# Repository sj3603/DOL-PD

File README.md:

# DOL-PD
A repository for the DOL-PD project, implementing USB-C PD support for the Gamecube!
<!--- Once you have a logo for the project, put it here!  -->
<br>
<p align="justify">DOL-PD is a power switch board replacement for the Gamecube. Bulky Gamecube power brick taking up media center space? Need a less cluttered solution for your tournament setups? Or do you just not have access to an old Gamecube power brick anymore? Just swap out your power board with the DOL-PD and enjoy the convenience of running your Gamecube with USB-C off of a readily available USB-PD wall charger! The project is completely open source. Make it, sell it, improve it, whatever you can think of! Bringing your Gamecube into the modern age has never been easier with this board.</p>
<br>
<p align="justify"><em>Make sure to reference the license information at the bottom for more info</em></p>

## PARTS LIST
* [Parts List](https://docs.google.com/spreadsheets/d/1rPVbGJX8rQoN7rI187_ITezFnfsLrNyPKBN4Mu2_UrU/edit?usp=sharing)

*Be sure to use the list of parts under the V1 sheet! V2 is still in development and does not have finalized components*

*Note: V1 currently utilizes HDR's 3D printed enclosure for the USB-C port. This enclosure is free to use under the CC BY-NC-ND 4.0 License, and therefore is free to use and redistribute, however is NOT USABLE FOR SALE. If you plan to use the DOL-PD to produce your own boards for sale, you must create your own USB-C shroud. In the future, I may release a modified V1 board that uses an alternative USB-C port with a 3D printed enclosure of my own design that will be free use.*

## BOARD ASSEMBLY INSTRUCTIONS
* [V1 Assembly Instructions](https://docs.google.com/document/d/1EoNc1ywIzINfLsrusN0_Oh6O5GwIsG2bt14rkOoPlFw/edit?usp=sharing)

*An in depth board assembly instructional video is coming soon! In the meantime, a rudimentary google doc will be provided in its place.*

## SYSTEM INSTALL INSTRUCTIONS
* [Install Instructions](https://docs.google.com/document/d/1jQh1p8UBnYjq_hNC_C3m5ErBJNf1RWyx2jeYvmH2byE/edit?usp=sharing)

## THE FUTURE OF DOL-PD
As of 9/3/2023, DOL-PD V1 has been completed and released publicly. Going forward, there are 3 main goals for the DOL-PD project:
* Create DOL-PD V2, utilizing an integrated buck converter to allow the Gamecube to take in 15V and step down to 12V. This should greatly increase compatibility with USB-PD chargers. V2 is also planned to utilize a different USB-C port from V1 to allow for a complete no-cut solution. I may also re-release V1 with this alternate USB-C port.
* Create DOL-PD Rev-B, giving users the option to transfer their original Gamecube power button to maintain original power button feel and functionality.
* Create DOL-PD EXT, an external version of DOL-PD that will not require any internal modification of the Gamecube. This will however require custom sourced Gamecube Male power port molds.

## SPECIAL THANKS
This project couldn't have been possible without help from members of the Bitbuilt community, but I'd also like to give a special thanks to these modders, go check them out!
* [YveltalGriffin](https://github.com/mackieks) - For his amazing help troubleshooting and teaching me about pcb design and routing! 
* [Greg from Laser Bear Industries](https://twitter.com/collingall) - For his help researching parts and understanding power management! (Check out his shop for some other cool GameCube mods!)
* [HDR](https://ko-fi.com/s/fa43244c34) - For providing the initial inspiration for this project with his GC_PD project (Check out his twitter for updates on future sales of his board!)

## LICENSE
<br />This work is licensed under a <a rel="license" href="http://creativecommons.org/licenses/by-sa/4.0/">Creative Commons Attribution-ShareAlike 4.0 International License</a>.

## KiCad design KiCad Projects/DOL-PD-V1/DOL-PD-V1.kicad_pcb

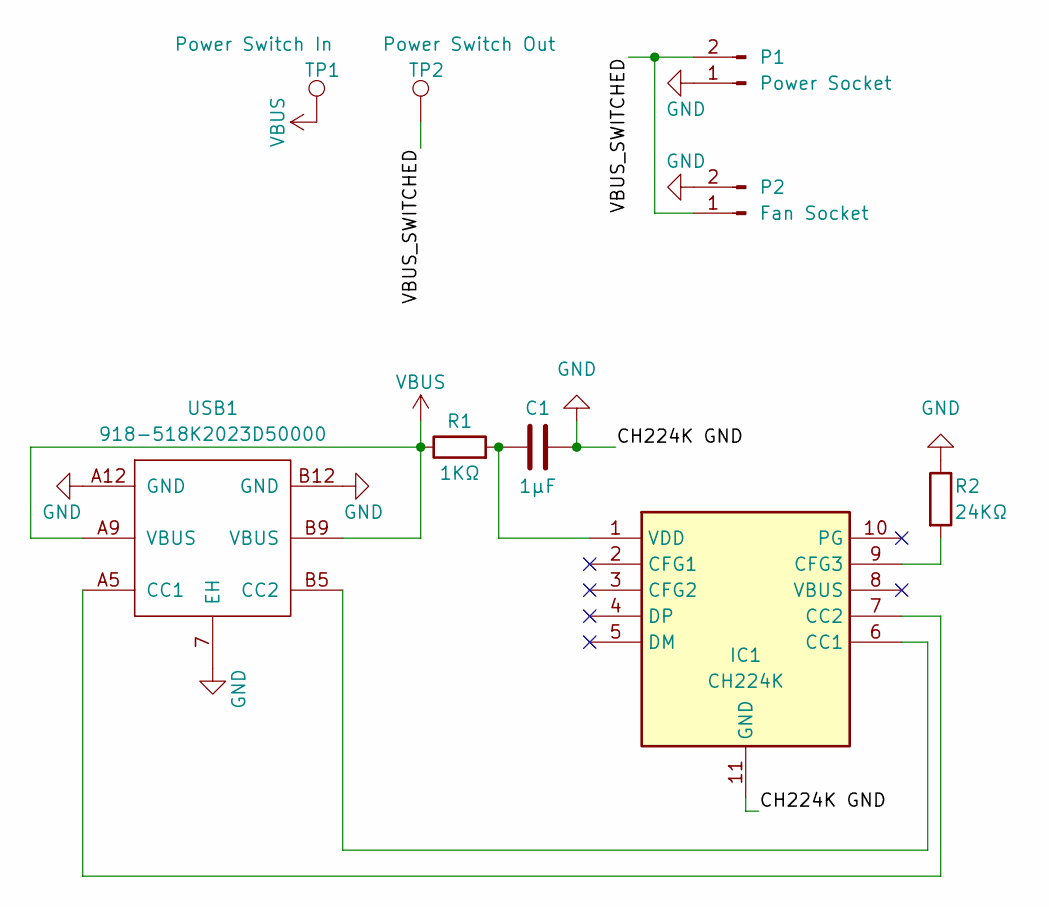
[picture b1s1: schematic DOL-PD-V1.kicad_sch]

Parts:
C1: 1µF; C_0603_1608Metric_Pad1.08x0.95mm_HandSolder
IC1: CH224K; SOP100P600X180-11N; Manufacturer_Part_Number CH224K
P1: Power Socket; JST_XH_B2B-XH-A_1x02_P2.50mm_Vertical
P2: Fan Socket; JST_PH_B2B-PH-K_1x02_P2.00mm_Vertical
R1: 1KΩ; R_0603_1608Metric_Pad0.98x0.95mm_HandSolder
R2: 24KΩ; R_0603_1608Metric_Pad0.98x0.95mm_HandSolder
TP1: Power Switch In; SolderWirePad_1x01_SMD_5x10mm
TP2: Power Switch Out; SolderWirePad_1x01_SMD_5x10mm
USB1: 918-518K2023D50000; USB-TYPE-C-TH_918-518K2023D5000X

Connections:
/CC1 USB: IC1.7 (CC2), USB1.A5 (CC1)
/CC2 USB: IC1.6 (CC1), USB1.B5 (CC2)
/CFG3: IC1.9 (CFG3), R2.2
/VBUS_SWITCHED: P1.2, P2.1, TP2.1
GND: C1.2, IC1.11 (GND), P1.1, P2.2, R2.1, USB1.7 (EH), USB1.A12 (GND), USB1.B12 (GND)
unnamed: C1.1, IC1.1 (VDD), R1.2
VBUS: R1.1, TP1.1, USB1.A9 (VBUS), USB1.B9 (VBUS)

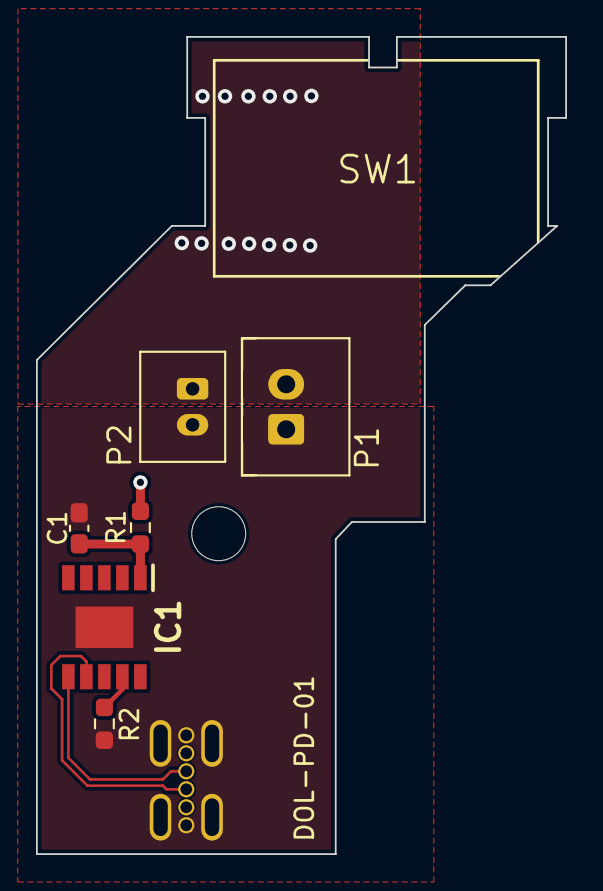
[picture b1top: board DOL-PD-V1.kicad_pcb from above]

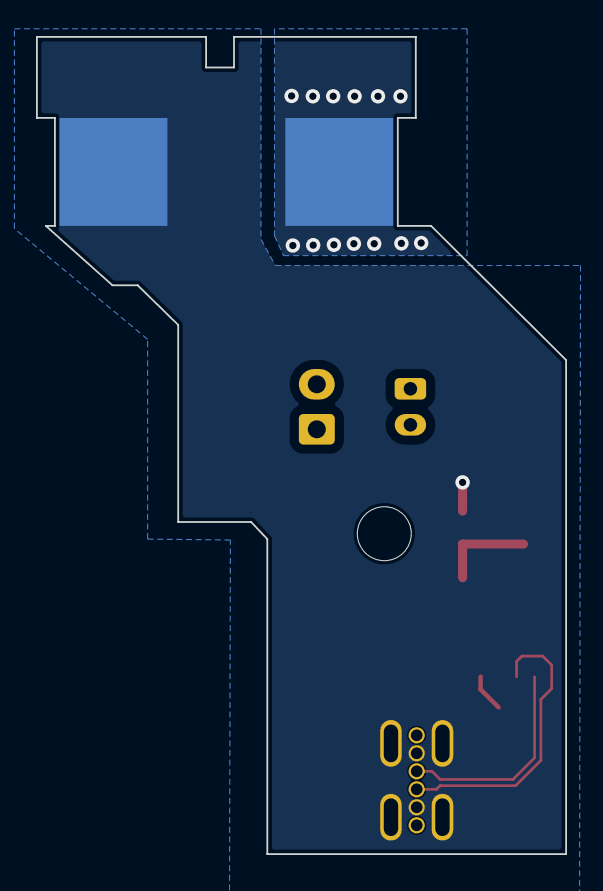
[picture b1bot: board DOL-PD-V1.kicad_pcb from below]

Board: 2 copper layers, 29.4 x 45.4 mm, 9 parts (2 on the bottom side), 7 nets.

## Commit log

2023-09-03 Update README.md
    Updated README for initial release
2023-09-03 V1 File upload
    - Initial upload of V1 KiCad files
2023-09-03 Update README.md
    Updated Special Thanks section with notes
2023-09-03 Update README.md
    Links now open in a new tab
2023-09-03 Update README.md
    Nevermind, opening in a new tab doesn't work
2023-09-03 Update README.md
    Updated publication date for official release!
